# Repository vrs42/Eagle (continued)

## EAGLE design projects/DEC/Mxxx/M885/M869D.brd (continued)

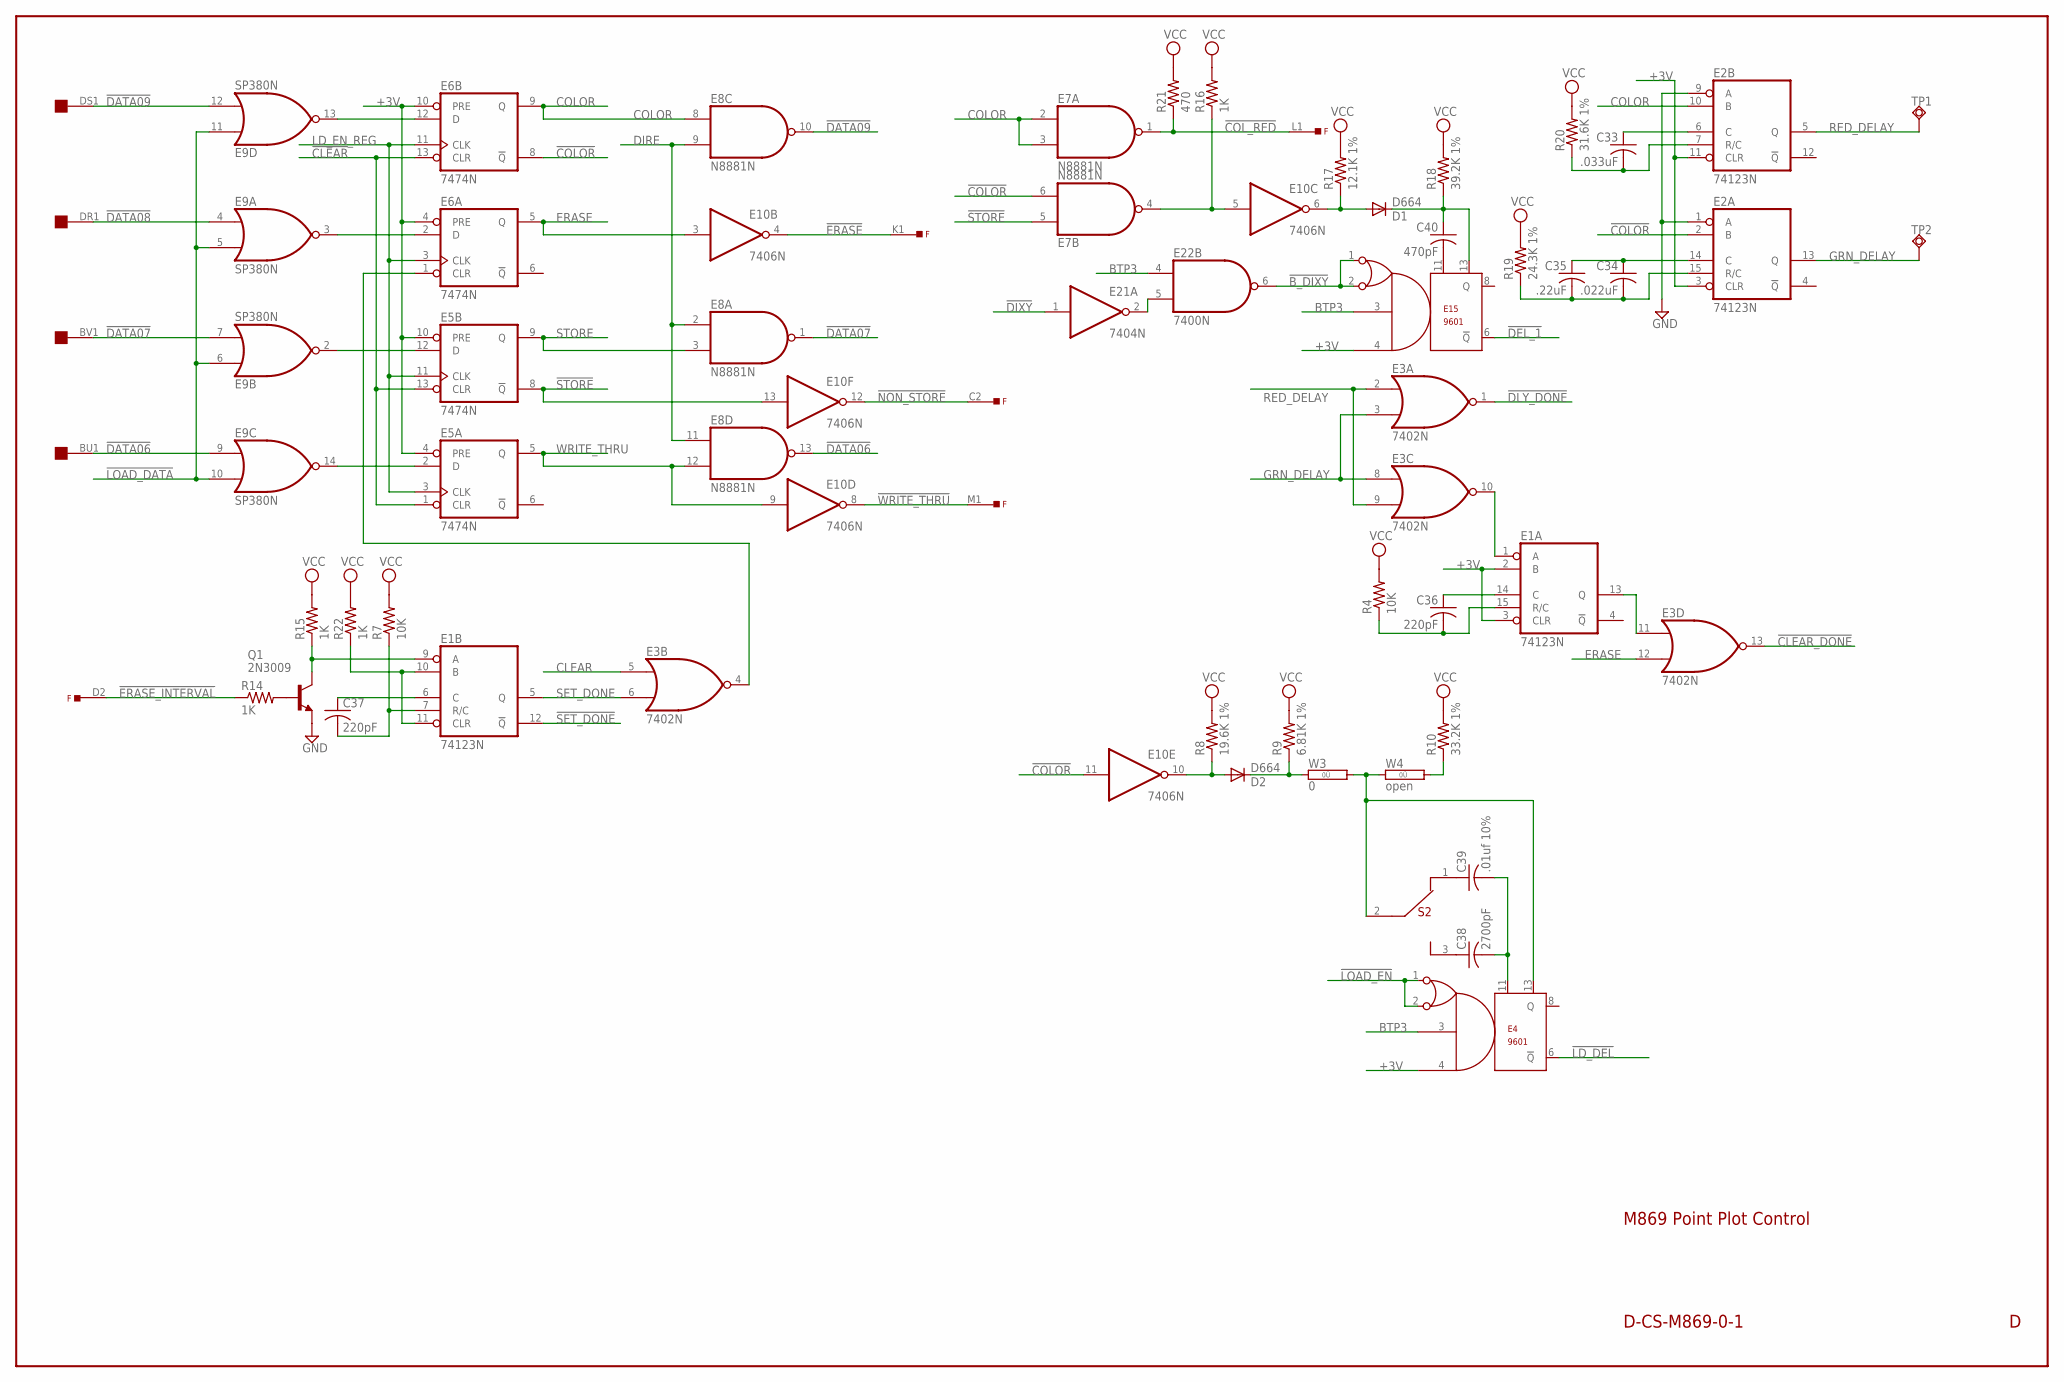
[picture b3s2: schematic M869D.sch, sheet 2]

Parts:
C33: .033uF; C325-137X374
C34: .022uF; C203-054-229
C35: .22uF; C203-054-229
C36, C37: 220pF; C063-025X075
C38: 2700pF; C102-043X133
C39: .01uf 10%; C063-025X075
C40: 470pF; C063-025X075
D1, D2: D664; DO35-10
E1, E2: 74123N; DIL16
E3: 7402N; DIL14
E4, E15: 9601; DIL14
E5, E6: 7474N; DIL14
E7, E8: N8881N; DIL14
E9: SP380N; DIL14
E10: 7406N; DIL14
E21: 7404N; DIL14
E22: 7400N; DIL14
F: EDGE-TOP; EDGE-CON2
OMNIBUS: QUAD; EDGE-CON8
Q1: 2N3009; TO18-
R4, R7: 10K; 0207/10
R8: 19.6K 1%; 0207/15
R9: 6.81K 1%; 0207/15
R10: 33.2K 1%; 0207/15
R14, R15, R16, R22: 1K; 0207/10
R17: 12.1K 1%; 0207/15
R18: 39.2K 1%; 0207/15
R19: 24.3K 1%; 0207/15
R20: 31.6K 1%; 0207/15
R21: 470; 0207/10
S2: 12-09698; 23-021
TP1, TP2: TPSQPAD1-17; P1-17
W3: 0; 0R/10
W4: open; 0R/10

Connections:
!B_DIXY: E15.1, E15.2, E22.6 (O); also elsewhere on the board
!CLEAR: E5.1 (CLR), E5.13 (CLR), E6.13 (CLR); also elsewhere on the board
!CLEAR_DONE: E3.13 (O); also elsewhere on the board
!COLOR: E2.2 (B), E6.8 (!Q), E7.6 (I1), E10.11 (I)
!COL_RED: E7.1 (O), F.L1, R21.1
!DATA06: E8.13 (O), E9.9 (I0), OMNIBUS.BU1
!DATA07: E8.1 (O), E9.7 (I1), OMNIBUS.BV1
!DATA08: E9.4 (I0), OMNIBUS.DR1
!DATA09: E8.10 (O), E9.12 (I1), OMNIBUS.DS1
!DEL_1: E15.6 (!Q); also elsewhere on the board
!DIXY: E21.1 (I); also elsewhere on the board
!DLY_DONE: E3.1 (O); also elsewhere on the board
!ERASE: E10.4 (O), F.K1
!ERASE_INTERVAL: F.D2, R14.1
!GREEN: D1.A, E10.6 (O), R17.1
!LD_DEL: E4.6 (!Q); also elsewhere on the board
!LOAD_DATA: E9.5 (I1), E9.6 (I0), E9.10 (I1), E9.11 (I0); also elsewhere on the board
!LOAD_EN: E4.1, E4.2; also elsewhere on the board
!NON_STORE: E10.12 (O), F.C2
!SET_DONE: E1.12 (!Q); also elsewhere on the board
!STORE: E5.8 (!Q), E7.5 (I0), E10.13 (I)
!WRITE_THRU: E10.8 (O), F.M1
+3V: E1.2 (B), E1.3 (CLR), E2.3 (CLR), E2.11 (CLR), E4.4, E5.4 (PRE), E5.10 (PRE), E6.4 (PRE), E6.10 (PRE), E15.4; also elsewhere on the board
BCOLOR: D2.A, E10.10 (O), R8.1
BTP3: E4.3, E15.3, E22.4 (I0); also elsewhere on the board
CLEAR: E3.5 (I0); also elsewhere on the board
COLOR: E2.10 (B), E6.9 (Q), E7.2 (I0), E7.3 (I1), E8.8 (I0)
DDONE: E1.13 (Q), E3.11 (I0)
DIRE: E8.2 (I0), E8.9 (I1), E8.11 (I0); also elsewhere on the board
DLY_DONE_L: E1.1 (A), E3.10 (O)
ERASE: E3.12 (I1), E6.5 (Q), E10.3 (I)
GND: E1.8 (GND), E2.1 (A), E2.8 (GND), E2.9 (A), E3.7 (GND), E4.7 (GND), E5.7 (GND), E6.7 (GND), E7.7 (GND), E8.7 (GND), E9.1 (GND), E10.7 (GND), E15.7 (GND), E21.7 (GND), E22.7 (GND), Q1.1 (E); also elsewhere on the board
GRN_DELAY: E2.13 (Q), E3.3 (I1), E3.8 (I0), TP2.TP
LD_EN_REG: E5.3 (CLK), E5.11 (CLK), E6.3 (CLK), E6.11 (CLK); also elsewhere on the board
unnamed: E21.2 (O), E22.5 (I1)
unnamed: E6.12 (D), E9.13 (O)
unnamed: E5.2 (D), E9.14 (O)
unnamed: E5.12 (D), E9.2 (O)
unnamed: E6.2 (D), E9.3 (O)
unnamed: E7.4 (O), E10.5 (I), R16.1
unnamed: E3.4 (O), E6.1 (CLR)
unnamed: C40.1, D1.C, E15.13, R18.1
unnamed: C40.2, E15.11
unnamed: C34.2, C35.2, E2.15 (R/C), R19.1
unnamed: C33.2, E2.7 (R/C), R20.1
unnamed: C33.1, E2.6 (C)
unnamed: C34.1, C35.1, E2.14 (C)
unnamed: C36.2, E1.15 (R/C), R4.1
unnamed: C36.1, E1.14 (C)
unnamed: Q1.2 (B), R14.2
unnamed: E1.9 (A), Q1.3 (C), R15.1
unnamed: E1.10 (B), E1.11 (CLR), R22.1
unnamed: C37.2, E1.7 (R/C), R7.1
unnamed: C37.1, E1.6 (C)
unnamed: D2.C, R9.1, W3.1
unnamed: E4.13, S2.2 (A2), W3.2, W4.1
unnamed: R10.1, W4.2
unnamed: C39.1, S2.1 (A1)
unnamed: C38.1, S2.3 (A3)
unnamed: C38.2, C39.2, E4.11
RED_DELAY: E2.5 (Q), E3.2 (I0), E3.9 (I1), TP1.TP
SET_DONE: E1.5 (Q), E3.6 (I1)
STORE: E5.9 (Q), E8.3 (I1)
VCC: E1.16 (VCC), E2.16 (VCC), E3.14 (VCC), E4.14 (VCC), E5.14 (VCC), E6.14 (VCC), E7.14 (VCC), E8.14 (VCC), E9.8 (VCC), E10.14 (VCC), E15.14 (VCC), E21.14 (VCC), E22.14 (VCC), R4.2, R7.2, R8.2, R9.2, R10.2, R15.2, R16.2, R17.2, R18.2, R19.2, R20.2, R21.2, R22.2; also elsewhere on the board
WRITE_THRU: E5.5 (Q), E8.12 (I1), E10.9 (I)

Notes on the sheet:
D-CS-M869-0-1
M869 Point Plot Control

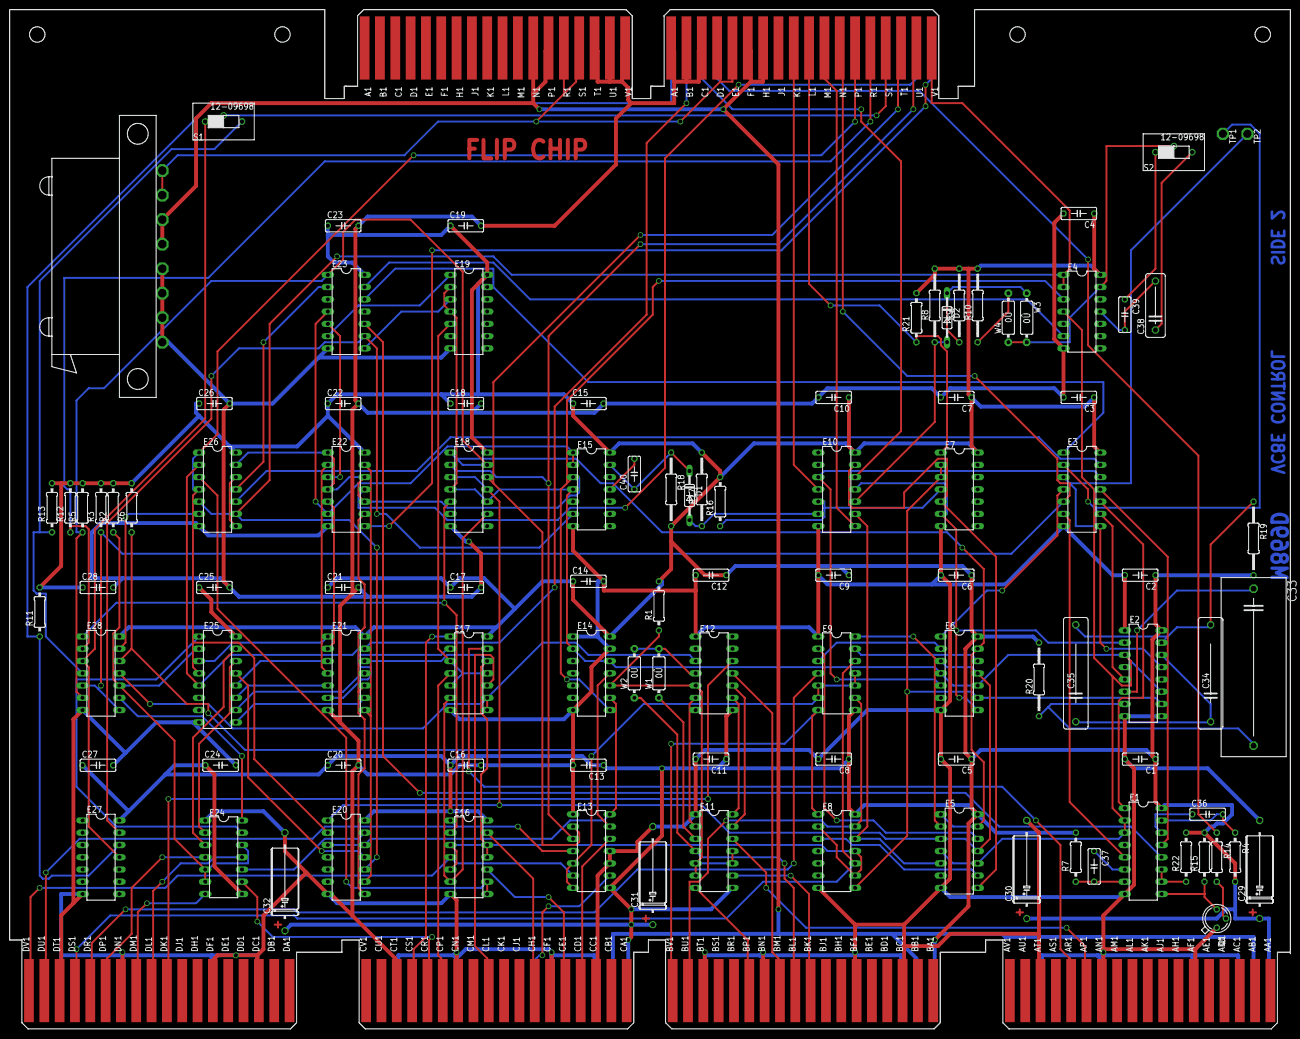
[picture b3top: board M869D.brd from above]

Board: 4 copper layers, 265.3 x 211.1 mm, 105 parts (0 on the bottom side), 132 nets.

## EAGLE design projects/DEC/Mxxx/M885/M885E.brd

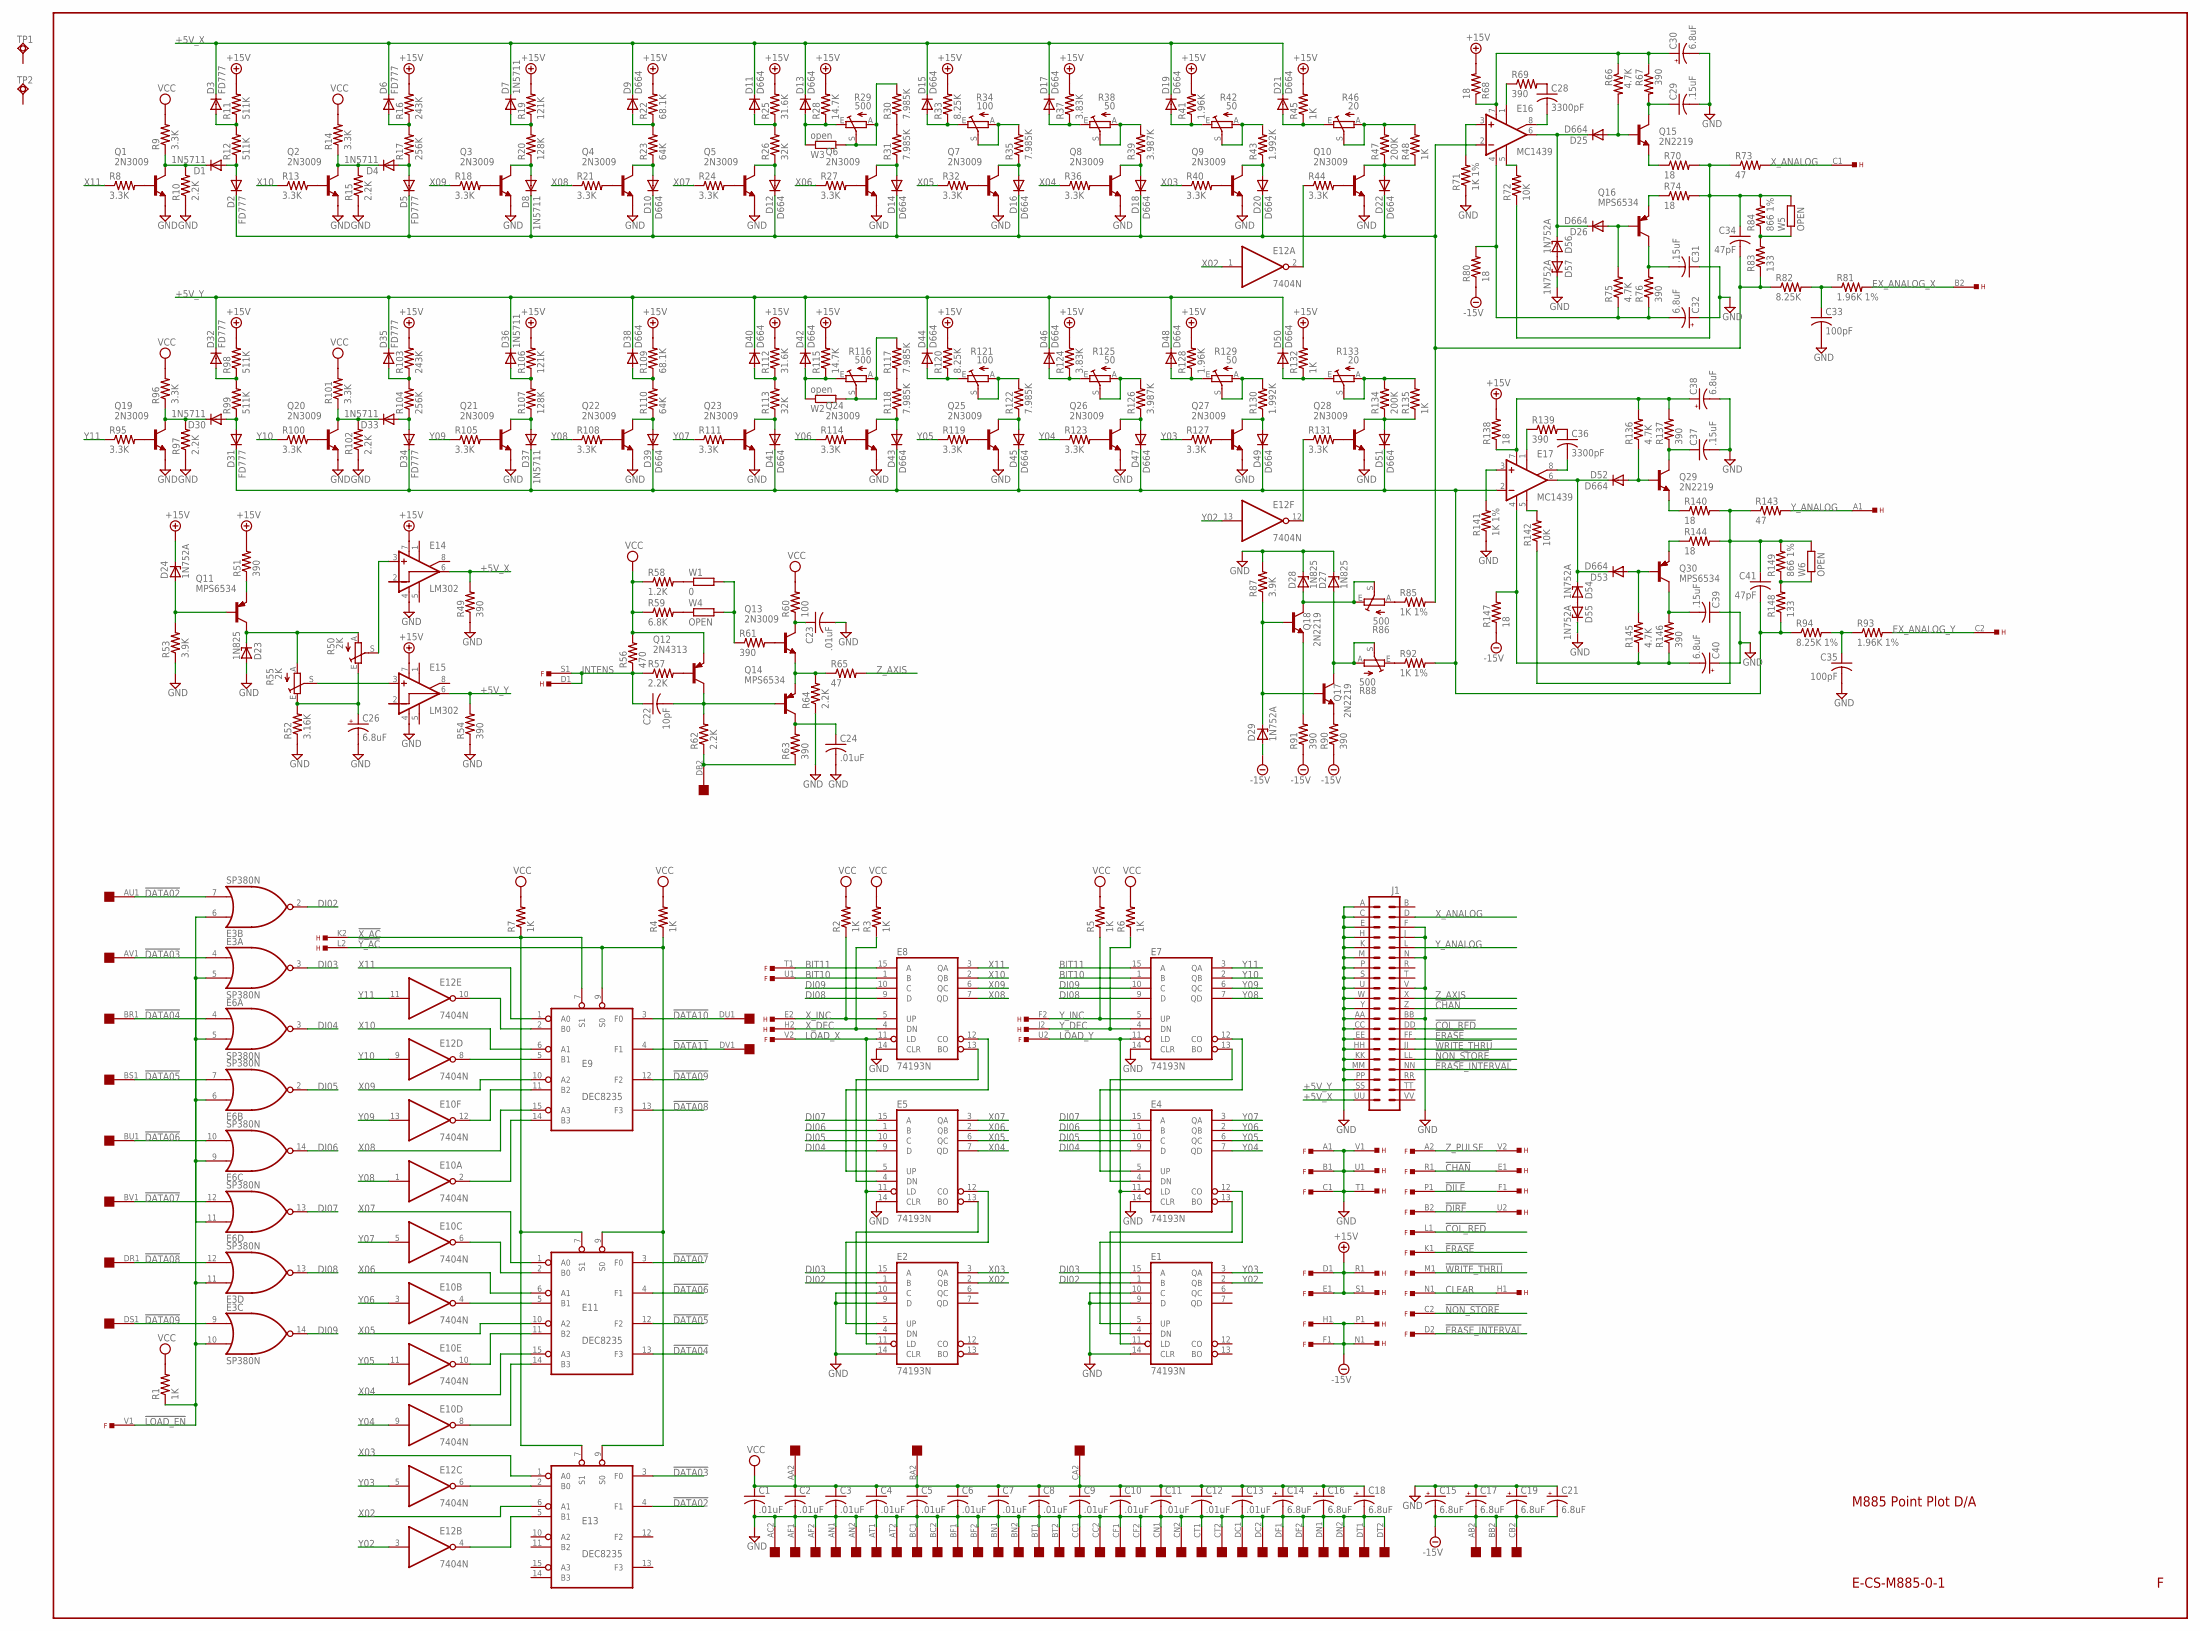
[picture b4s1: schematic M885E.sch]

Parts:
C1, C2, C3, C4, C5, C6, C7, C8, C9, C10, C11, C12, C13, C23, C24: .01uF; C063-025X075
C14, C15, C16, C17, C18, C19, C21, C26, C30, C32, C38, C40: 6.8uF; E12-8
C22: 10pF; C063-025X075
C28, C36: 3300pF; C150-054X183
C29, C31, C37, C39: .15uF; C150-054X183
C33, C35: 100pF; C063-025X075
C34, C41: 47pF; C063-025X075
D1, D4, D7, D8, D30, D33, D36, D37: 1N5711; DO35-10
D2, D3, D5, D6, D31, D32, D34, D35: FD777; DO35-10
D9, D10, D11, D12, D13, D14, D15, D16, D17, D18, D19, D20, D21, D22, D25, D26, D38, D39, D40, D41, D42, D43, D44, D45, D46, D47, D48, D49, D50, D51, D52, D53: D664; DO35-10
D23, D27, D28: 1N825; DO35Z10
D24, D29, D54, D55, D56, D57: 1N752A; DO35Z10
E1, E2, E4, E5, E7, E8: 74193N; DIL16
E3, E6: SP380N; DIL14
E9, E11, E13: DEC8235; DIL16
E10, E12: 7404N; DIL14
E14, E15: LM302; TO99
E16, E17: MC1439; TO99
F: EDGE-TOP; EDGE-CON2
H: EDGE-TOP; EDGE-CON2
J1: DEC40PINH
OMNIBUS: QUAD; EDGE-CON8
Q1, Q2, Q3, Q4, Q5, Q6, Q7, Q8, Q9, Q10, Q13, Q19, Q20, Q21, Q22, Q23, Q24, Q25, Q26, Q27, Q28: 2N3009; TO5
Q11, Q14, Q16, Q30: MPS6534; TO5
Q12: 2N4313; TO5
Q15, Q17, Q18, Q29: 2N2219; TO5
R1, R2, R3, R4, R5, R6, R7: 1K; 0207/10
R8, R9, R13, R14, R18, R21, R24, R27, R32, R36, R40, R44, R95, R96, R100, R101, R105, R108, R111, R114, R119, R123, R127, R131: 3.3K; 0207/10
R10, R15, R57, R62, R64, R97, R102: 2.2K; 0207/10
R11, R12, R98, R99: 511K; 0207/15
R16, R103: 243K; 0207/15
R17, R104: 256K; 0207/15
R19, R106: 121K; 0207/15
R20, R107: 128K; 0207/15
R22, R109: 68.1K; 0207/15
R23, R110: 64K; 0207/15
R25, R112: 31.6K; 0207/15
R26, R113: 32K; 0207/15
R28, R115: 14.7K; 0207/15
R29, R116: 500; S75P
R30, R31, R35, R117, R118, R122: 7.985K; 0207/15
R33, R82, R120: 8.25K; 0207/15
R34, R121: 100; S75P
R37, R124: 3.83K; 0207/15
R38, R42, R125, R129: 50; S75P
R39, R126: 3.987K; 0207/15
R41, R128: 1.96K; 0207/15
R43, R130: 1.992K; 0207/15
R45, R48, R132, R135: 1K; 0207/15
R46, R133: 20; S75P
R47, R134: 200K; 0207/15
R49, R51, R54, R61, R63, R67, R69, R76, R90, R91, R137, R139, R146: 390; 0207/10
R50, R55: 2K; SP19L
R52: 3.16K; 0207/15
R53, R87: 3.9K; 0207/10
R56: 470; 0207/10
R58: 1.2K; 0207/10
R59: 6.8K; 0207/10
R60: 100; 0207/10
R65, R73, R143: 47; 0207/10
R66, R75, R136, R145: 4.7K; 0207/10
R68, R70, R74, R80, R138, R140, R144, R147: 18; 0207/10
R71, R85, R92, R141: 1K 1%; 0207/15
R72, R142: 10K; 0207/10
R81, R93: 1.96K 1%; 0207/15
R83, R148: 133; 0207/15
R84, R149: 866 1%; 0207/15
R86, R88: 500; SP19L
R94: 8.25K 1%; 0207/10
TP1, TP2: TPSQPAD1-17; P1-17
W1: 0; 0207/10
W2, W3: open; 0207/10
W4, W5, W6: OPEN; 0207/10

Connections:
!CHAN: F.R1, H.E1, J1.Z (22)
!COL_RED: F.L1, J1.DD (26)
!DATA02: E3.7 (I1), E13.4 (F1), OMNIBUS.AU1
!DATA03: E3.4 (I0), E13.3 (F0), OMNIBUS.AV1
!DATA04: E6.4 (I0), E11.13 (F3), OMNIBUS.BR1
!DATA05: E6.7 (I1), E11.12 (F2), OMNIBUS.BS1
!DATA06: E6.10 (I1), E11.4 (F1), OMNIBUS.BU1
!DATA07: E6.12 (I1), E11.3 (F0), OMNIBUS.BV1
!DATA08: E3.12 (I1), E9.13 (F3), OMNIBUS.DR1
!DATA09: E3.9 (I0), E9.12 (F2), OMNIBUS.DS1
!DATA10: E9.3 (F0), OMNIBUS.DU1
!DATA11: E9.4 (F1), OMNIBUS.DV1
!DILE: F.P1, H.F1
!DIRE: F.B2, H.U2
!ERASE: F.K1, J1.FF (28)
!ERASE_INTERVAL: F.D2, J1.NN (34)
!LOAD_EN: E3.5 (I1), E3.6 (I0), E3.10 (I1), E3.11 (I0), E6.5 (I1), E6.6 (I0), E6.9 (I0), E6.11 (I0), F.V1, R1.1
!NON_STORE: F.C2, J1.LL (32)
!WRITE_THRU: F.M1, J1.JJ (30)
!X_AC: E9.7 (S1), E11.7 (S1), E13.7 (S1), H.K2, R7.1
!Y_AC: E9.9 (S0), E11.9 (S0), E13.9 (S0), H.L2, R4.1
+5V_X: D3.C, D6.C, D7.C, D9.C, D11.C, D13.C, D15.C, D17.C, D19.C, D21.C, E14.6 (OUT), J1.UU (39), R49.2
+5V_Y: D32.C, D35.C, D36.C, D38.C, D40.C, D42.C, D44.C, D46.C, D48.C, D50.C, E15.6 (OUT), J1.SS (37), R54.2
+15V: D24.C, E14.7 (V+), E15.7 (V+), F.D1, F.E1, H.R1, H.S1, R11.2, R16.2, R19.2, R22.2, R25.2, R28.2, R33.2, R37.2, R41.2, R45.2, R51.2, R68.2, R98.2, R103.2, R106.2, R109.2, R112.2, R115.2, R120.2, R124.2, R128.2, R132.2, R138.2
-15V: C15.-, C17.-, C19.-, C21.-, D29.A, F.F1, F.H1, H.N1, H.P1, OMNIBUS.AB2, OMNIBUS.BB2, OMNIBUS.CB2, R80.1, R90.1, R91.1, R147.1
BIT10: E7.1 (B), E8.1 (B), F.U1
BIT11: E7.15 (A), E8.15 (A), F.T1
CLEAR: F.N1, H.H1
DI02: E1.1 (B), E2.1 (B), E3.2 (O)
DI03: E1.15 (A), E2.15 (A), E3.3 (O)
DI04: E4.9 (D), E5.9 (D), E6.3 (O)
DI05: E4.10 (C), E5.10 (C), E6.2 (O)
DI06: E4.1 (B), E5.1 (B), E6.14 (O)
DI07: E4.15 (A), E5.15 (A), E6.13 (O)
DI08: E3.13 (O), E7.9 (D), E8.9 (D)
DI09: E3.14 (O), E7.10 (C), E8.10 (C)
EX_ANALOG_X: H.B2, R81.2
EX_ANALOG_Y: H.C2, R93.2
GND: C1.2, C2.2, C3.2, C4.2, C5.2, C6.2, C7.2, C8.2, C9.2, C10.2, C11.2, C12.2, C13.2, C14.-, C15.+, C16.-, C17.+, C18.-, C19.+, C21.+, C23.2, C24.2, C26.-, C29.2, C30.-, C31.1, C32.+, C33.2, C35.2, C37.2, C38.-, C39.1, C40.+, D23.A, D27.C, D28.C, D55.C, D57.C, E1.8 (GND), E1.9 (D), E1.10 (C), E1.14 (CLR), E2.8 (GND), E2.9 (D), E2.10 (C), E2.14 (CLR), E3.1 (GND), E4.8 (GND), E4.14 (CLR), E5.8 (GND), E5.14 (CLR), E6.1 (GND), E7.8 (GND), E7.14 (CLR), E8.8 (GND), E8.14 (CLR), E9.8 (GND), E10.7 (GND), E11.8 (GND), E12.7 (GND), E13.8 (GND), E14.4 (V-), E15.4 (V-), F.A1, F.B1, F.C1, H.T1, H.U1, H.V1, J1.A (1), J1.AA (23), J1.BB (24), J1.C (3), J1.CC (25), J1.E (5), J1.EE (27), J1.F (6), J1.H (7), J1.HH (29), J1.J (8), J1.K (9), J1.KK (31), J1.M (11), J1.MM (33), J1.N (12), J1.P (13), J1.PP (35), J1.S (15), J1.U (17), J1.V (18), J1.W (19), J1.Y (21), OMNIBUS.AC2, OMNIBUS.AF1, OMNIBUS.AF2, OMNIBUS.AN1, OMNIBUS.AN2, OMNIBUS.AT1, OMNIBUS.AT2, OMNIBUS.BC1, OMNIBUS.BC2, OMNIBUS.BF1, OMNIBUS.BF2, OMNIBUS.BN1, OMNIBUS.BN2, OMNIBUS.BT1, OMNIBUS.BT2, OMNIBUS.CC1, OMNIBUS.CC2, OMNIBUS.CF1, OMNIBUS.CF2, OMNIBUS.CN1, OMNIBUS.CN2, OMNIBUS.CT1, OMNIBUS.CT2, OMNIBUS.DC1, OMNIBUS.DC2, OMNIBUS.DF1, OMNIBUS.DF2, OMNIBUS.DN1, OMNIBUS.DN2, OMNIBUS.DT1, OMNIBUS.DT2, Q1.1 (E), Q2.1 (E), Q3.1 (E), Q4.1 (E), Q5.1 (E), Q6.1 (E), Q7.1 (E), Q8.1 (E), Q9.1 (E), Q10.1 (E), Q19.1 (E), Q20.1 (E), Q21.1 (E), Q22.1 (E), Q23.1 (E), Q24.1 (E), Q25.1 (E), Q26.1 (E), Q27.1 (E), Q28.1 (E), R10.1, R15.1, R49.1, R52.1, R53.1, R54.1, R64.1, R71.1, R87.2, R97.1, R102.1, R141.1
INTENS: C22.1, F.S1, H.D1, R56.1, R57.1
LOAD_X: E2.11 (LD), E5.11 (LD), E8.11 (LD), F.V2
LOAD_Y: E1.11 (LD), E4.11 (LD), E7.11 (LD), F.U2
unnamed: E9.2 (B0), E12.10 (O)
unnamed: E9.5 (B1), E12.8 (O)
unnamed: E9.11 (B2), E10.12 (O)
unnamed: E9.14 (B3), E10.2 (O)
unnamed: E10.6 (O), E11.2 (B0)
unnamed: E1.4 (DN), E4.13 (BO)
unnamed: E10.4 (O), E11.5 (B1)
unnamed: E10.10 (O), E11.11 (B2)
unnamed: E10.8 (O), E11.14 (B3)
unnamed: E1.5 (UP), E4.12 (CO)
unnamed: E12.6 (O), E13.2 (B0)
unnamed: E4.4 (DN), E7.13 (BO)
unnamed: E12.4 (O), E13.5 (B1)
unnamed: E4.5 (UP), E7.12 (CO)
unnamed: D3.A, R11.1, R12.2
unnamed: D1.A, D2.A, R12.1
unnamed: D7.A, R19.1, R20.2
unnamed: D13.A, R28.1, R29.E, W3.1
unnamed: Q1.2 (B), R8.2
unnamed: D1.C, Q1.3 (C), R9.1, R10.2
unnamed: E2.4 (DN), E5.13 (BO)
unnamed: E2.5 (UP), E5.12 (CO)
unnamed: E5.4 (DN), E8.13 (BO)
unnamed: E5.5 (UP), E8.12 (CO)
unnamed: D6.A, R16.1, R17.2
unnamed: D4.A, D5.A, R17.1
unnamed: C34.2, D2.C, D5.C, D8.C, D10.C, D12.C, D14.C, D16.C, D18.C, D20.C, D22.C, E16.2 (-IN), R82.1, R83.1, R85.2
unnamed: Q2.2 (B), R13.2
unnamed: D4.C, Q2.3 (C), R14.1, R15.2
unnamed: R30.1, R31.2
unnamed: D8.A, Q3.3 (C), R20.1
unnamed: Q3.2 (B), R18.2
unnamed: D32.A, R98.1, R99.2
unnamed: R29.A, R29.S, R30.2, W3.2
unnamed: R34.A, R34.S, R35.2
unnamed: D9.A, R22.1, R23.2
unnamed: D10.A, Q4.3 (C), R23.1
unnamed: Q4.2 (B), R21.2
unnamed: D30.A, D31.A, R99.1
unnamed: D17.A, R37.1, R38.E
unnamed: R42.A, R42.S, R43.2
unnamed: D11.A, R25.1, R26.2
unnamed: D12.A, Q5.3 (C), R26.1
unnamed: Q5.2 (B), R24.2
unnamed: Q19.2 (B), R95.2
unnamed: R46.A, R46.S, R47.2, R48.2
unnamed: D30.C, Q19.3 (C), R96.1, R97.2
unnamed: D35.A, R103.1, R104.2
unnamed: D14.A, Q6.3 (C), R31.1
unnamed: Q6.2 (B), R27.2
unnamed: D33.A, D34.A, R104.1
unnamed: C41.2, D31.C, D34.C, D37.C, D39.C, D41.C, D43.C, D45.C, D47.C, D49.C, D51.C, E17.2 (-IN), R92.2, R94.1, R148.1
unnamed: Q20.2 (B), R100.2
unnamed: D15.A, R33.1, R34.E
unnamed: D16.A, Q7.3 (C), R35.1
unnamed: Q7.2 (B), R32.2
unnamed: D33.C, Q20.3 (C), R101.1, R102.2
unnamed: D36.A, R106.1, R107.2
unnamed: D37.A, Q21.3 (C), R107.1
unnamed: R38.A, R38.S, R39.2
unnamed: D18.A, Q8.3 (C), R39.1
unnamed: Q8.2 (B), R36.2
unnamed: Q21.2 (B), R105.2
unnamed: D38.A, R109.1, R110.2
unnamed: D39.A, Q22.3 (C), R110.1
unnamed: D19.A, R41.1, R42.E
unnamed: D20.A, Q9.3 (C), R43.1
unnamed: Q9.2 (B), R40.2
unnamed: Q22.2 (B), R108.2
unnamed: D40.A, R112.1, R113.2
unnamed: D41.A, Q23.3 (C), R113.1
unnamed: D21.A, R45.1, R46.E
unnamed: D22.A, Q10.3 (C), R47.1, R48.1
unnamed: Q10.2 (B), R44.2
unnamed: Q23.2 (B), R111.2
unnamed: E12.2 (O), R44.1
unnamed: D43.A, Q24.3 (C), R118.1
unnamed: Q24.2 (B), R114.2
unnamed: D44.A, R120.1, R121.E
unnamed: D45.A, Q25.3 (C), R122.1
unnamed: Q25.2 (B), R119.2
unnamed: R125.A, R125.S, R126.2
unnamed: D47.A, Q26.3 (C), R126.1
unnamed: Q26.2 (B), R123.2
unnamed: D48.A, R128.1, R129.E
unnamed: D49.A, Q27.3 (C), R130.1
unnamed: Q27.2 (B), R127.2
unnamed: D50.A, R132.1, R133.E
unnamed: D51.A, Q28.3 (C), R134.1, R135.1
unnamed: Q28.2 (B), R131.2
unnamed: E12.12 (O), R131.1
unnamed: D42.A, R115.1, R116.E, W2.1
unnamed: R117.1, R118.2
unnamed: R116.A, R116.S, R117.2, W2.2
unnamed: R121.A, R121.S, R122.2
unnamed: D46.A, R124.1, R125.E
unnamed: R129.A, R129.S, R130.2
unnamed: R133.A, R133.S, R134.2, R135.2
unnamed: D24.A, Q11.2 (B), R53.2
unnamed: Q11.1 (E), R51.1
unnamed: D23.C, Q11.3 (C), R50.A, R55.A
unnamed: C26.+, R50.E, R52.2, R55.E
unnamed: E15.3 (+IN), R55.S
unnamed: Q12.2 (B), R57.2
unnamed: E14.3 (+IN), R50.S
unnamed: C22.2, Q12.3 (C), Q14.2 (B), R62.2
unnamed: OMNIBUS.DB2, R62.1, R63.1
unnamed: C24.1, Q14.3 (C), R63.2
unnamed: Q13.1 (E), Q14.1 (E), R64.2, R65.1
unnamed: R58.2, W1.1
unnamed: R59.2, W4.1
unnamed: Q13.2 (B), R61.2
unnamed: R61.1, W1.2, W4.2
unnamed: C30.+, E16.7 (V+), R66.1, R67.1, R68.1
unnamed: C23.1, Q13.3 (C), R60.1
unnamed: E16.1 (ON1), R69.1
unnamed: C28.1, R69.2
unnamed: C28.2, E16.8 (ON2)
unnamed: D25.A, Q15.2 (B), R66.2
unnamed: D26.A, Q16.2 (B), R75.2
unnamed: D25.C, D26.C, D56.C, E16.6 (OUT)
unnamed: D56.A, D57.A
unnamed: C32.-, E16.4 (V-), R75.1, R76.1, R80.2
unnamed: C29.1, Q15.3 (C), R67.2
unnamed: C31.2, Q16.3 (C), R76.2
unnamed: Q16.1 (E), R74.1
unnamed: E16.5 (OPT), R72.2
unnamed: C34.1, R70.2, R72.1, R73.1, R74.2, R84.2, W5.2
unnamed: Q15.1 (E), R70.1
unnamed: C33.1, R81.1, R82.2
unnamed: R83.2, R84.1, W5.1
unnamed: E16.3 (+IN), R71.2
unnamed: R85.1, R86.A
unnamed: D54.A, D55.A
unnamed: D29.C, Q17.2 (B), Q18.2 (B), R87.1
unnamed: Q18.1 (E), R91.2
unnamed: Q17.1 (E), R90.2
unnamed: D28.A, Q18.3 (C), R86.E, R86.S
unnamed: D27.A, Q17.3 (C), R88.A, R88.S
unnamed: R88.E, R92.1
unnamed: C38.+, E17.7 (V+), R136.2, R137.2, R138.1
unnamed: C36.1, R139.2
unnamed: C36.2, E17.8 (ON2)
unnamed: E17.1 (ON1), R139.1
unnamed: D52.C, D53.C, D54.C, E17.6 (OUT)
unnamed: D52.A, Q29.2 (B), R136.1
unnamed: C37.1, Q29.3 (C), R137.1
unnamed: D53.A, Q30.2 (B), R145.2
unnamed: C39.2, Q30.3 (C), R146.2
unnamed: C40.-, E17.4 (V-), R145.1, R146.1, R147.2
unnamed: E17.5 (OPT), R142.2
unnamed: C41.1, R140.2, R142.1, R143.1, R144.2, R149.2, W6.2
unnamed: Q30.1 (E), R144.1
unnamed: Q29.1 (E), R140.1
unnamed: E17.3 (+IN), R141.2
unnamed: R148.2, R149.1, W6.1
unnamed: C35.1, R93.1, R94.2
VCC: C1.1, C2.1, C3.1, C4.1, C5.1, C6.1, C7.1, C8.1, C9.1, C10.1, C11.1, C12.1, C13.1, C14.+, C16.+, C18.+, E1.16 (VCC), E2.16 (VCC), E3.8 (VCC), E4.16 (VCC), E5.16 (VCC), E6.8 (VCC), E7.16 (VCC), E8.16 (VCC), E9.16 (VCC), E10.14 (VCC), E11.16 (VCC), E12.14 (VCC), E13.16 (VCC), OMNIBUS.AA2, OMNIBUS.BA2, OMNIBUS.CA2, Q12.1 (E), R1.2, R2.2, R3.2, R4.2, R5.2, R6.2, R7.2, R9.2, R14.2, R56.2, R58.1, R59.1, R60.2, R96.2, R101.2
X02: E2.2 (QB), E12.1 (I), E13.6 (A1)
X03: E2.3 (QA), E13.1 (A0), R40.1
X04: E5.7 (QD), E11.15 (A3), R36.1
X05: E5.6 (QC), E11.10 (A2), R32.1
X06: E5.2 (QB), E11.6 (A1), R27.1
X07: E5.3 (QA), E11.1 (A0), R24.1
X08: E8.7 (QD), E9.15 (A3), R21.1
X09: E8.6 (QC), E9.10 (A2), R18.1
X10: E8.2 (QB), E9.6 (A1), R13.1
X11: E8.3 (QA), E9.1 (A0), R8.1
X_ANALOG: H.C1, J1.D (4), R73.2
X_DEC: E8.4 (DN), H.H2, R3.1
X_INC: E8.5 (UP), H.E2, R2.1
Y02: E1.2 (QB), E12.3 (I), E12.13 (I)
Y03: E1.3 (QA), E12.5 (I), R127.1
Y04: E4.7 (QD), E10.9 (I), R123.1
Y05: E4.6 (QC), E10.11 (I), R119.1
Y06: E4.2 (QB), E10.3 (I), R114.1
Y07: E4.3 (QA), E10.5 (I), R111.1
Y08: E7.7 (QD), E10.1 (I), R108.1
Y09: E7.6 (QC), E10.13 (I), R105.1
Y10: E7.2 (QB), E12.9 (I), R100.1
Y11: E7.3 (QA), E12.11 (I), R95.1
Y_ANALOG: H.A1, J1.L (10), R143.2
Y_DEC: E7.4 (DN), H.J2, R6.1
Y_INC: E7.5 (UP), H.F2, R5.1
Z_AXIS: J1.X (20), R65.2
Z_PULSE: F.A2, H.V2

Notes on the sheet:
E-CS-M885-0-1
M885 Point Plot D/A

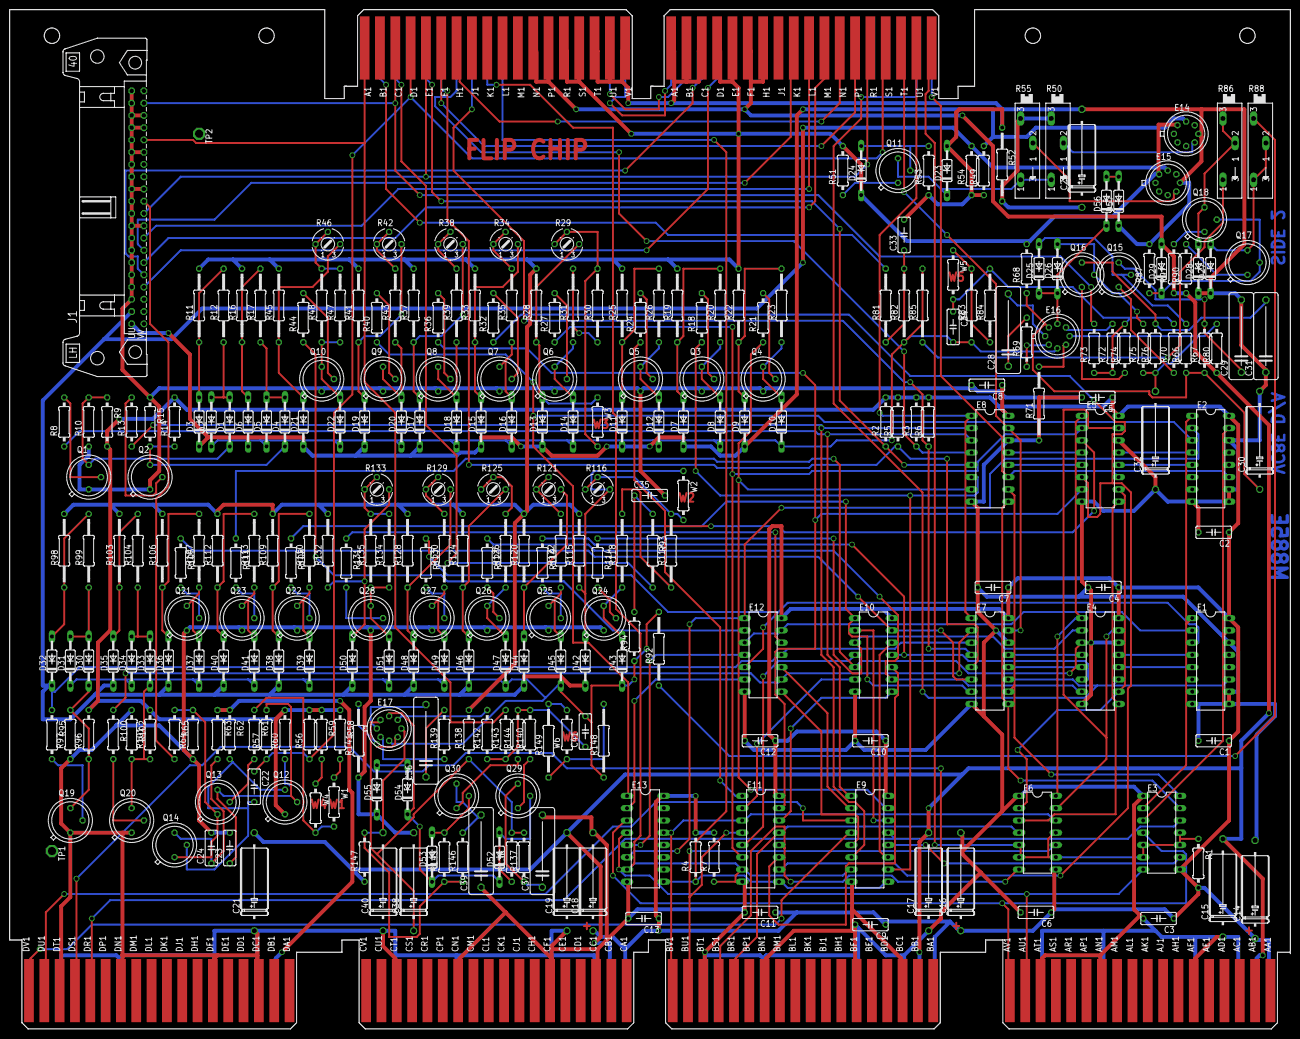
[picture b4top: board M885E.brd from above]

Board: 4 copper layers, 265.3 x 211.1 mm, 299 parts (0 on the bottom side), 228 nets.
